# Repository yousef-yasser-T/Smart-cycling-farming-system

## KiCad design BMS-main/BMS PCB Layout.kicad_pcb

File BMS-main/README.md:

# BMS
# EV Battery Management System

Hardware design of a Battery Management System for Electric Vehicle applications.

## Overview

Designed the BMS schematic and PCB using KiCad, with manufacturing-ready Gerber files.

## Key Features

- Cell voltage monitoring
- Battery protection
- Temperature monitoring
- Current monitoring
- Cell balancing
- BMS control and monitoring

## Design

- Schematic: KiCad
- PCB Layout: KiCad
- Manufacturing: Gerber files
- BMS IC: TI BQ76920

## Files

| File | Description |
|---|---|
| `.kicad_sch` | BMS schematic |
| `.kicad_pcb` | PCB layout |
| `.zip` | Gerber manufacturing files |
| `.pdf` | BQ76920 datasheet |

## Focus Areas

**EV Systems | BMS | PCB Design | Battery Electronics | Embedded Systems**

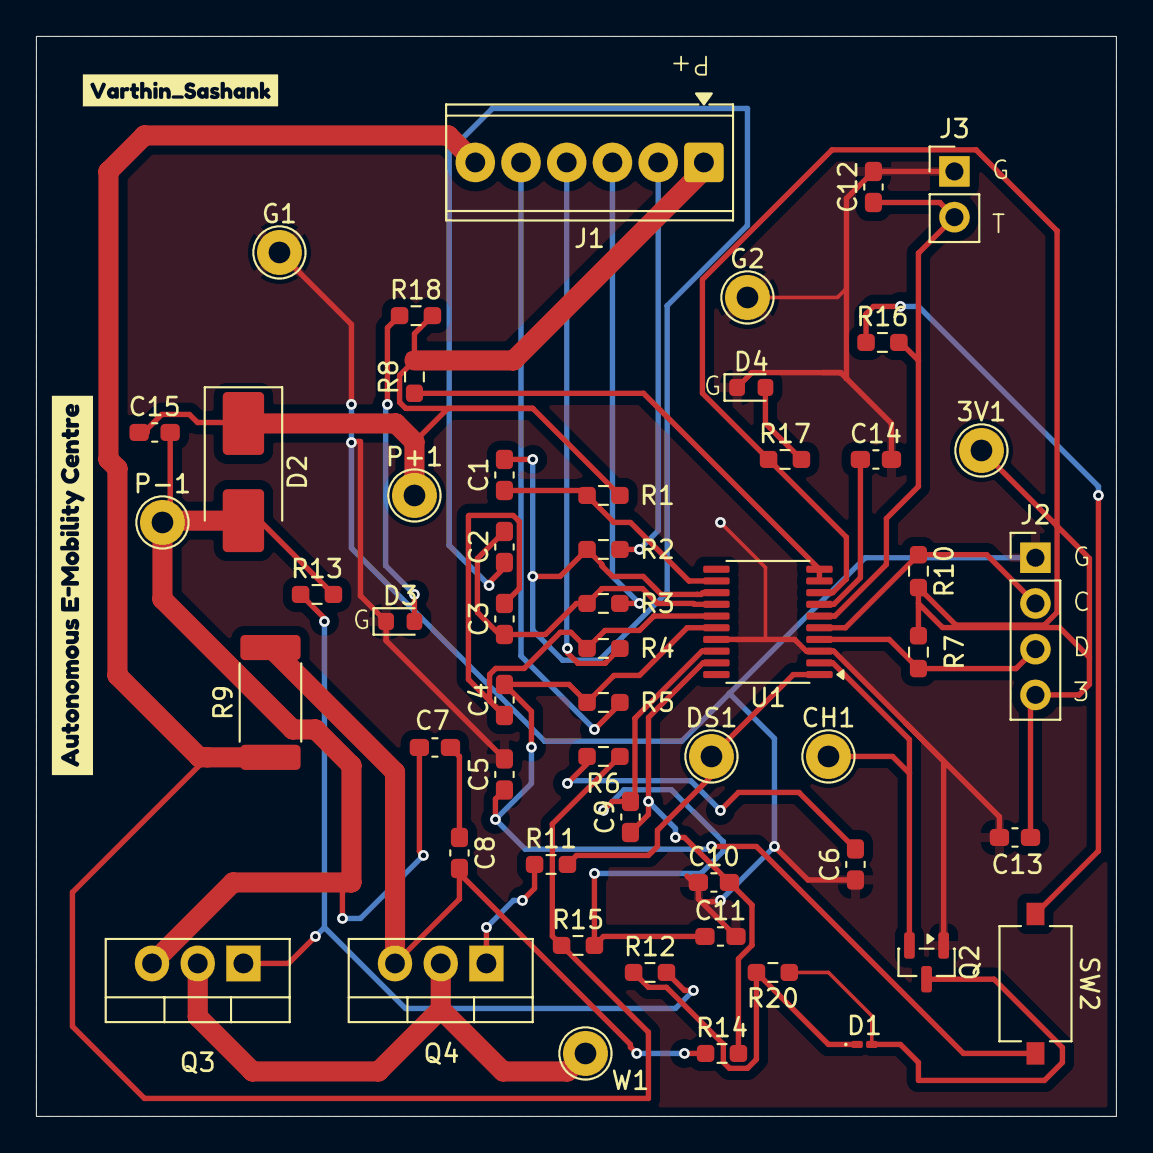
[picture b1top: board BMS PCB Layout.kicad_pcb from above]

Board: 2 copper layers, 60.0 x 60.0 mm, 56 parts (0 on the bottom side), 34 nets.

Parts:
3V1: TestPoint; TestPoint_THTPad_D2.5mm_Drill1.2mm
C1, C2, C3, C4, C5, C6, C9, C10, C11, C12, C14: 1uf; C_0603_1608Metric_Pad1.08x0.95mm_HandSolder
C7, C8: 0.1uf; C_0603_1608Metric_Pad1.08x0.95mm_HandSolder
C13: 4.7k; C_0603_1608Metric_Pad1.08x0.95mm_HandSolder
C15: 2.2uf; C_0603_1608Metric_Pad1.08x0.95mm_HandSolder
CH1: TestPoint; TestPoint_THTPad_D2.5mm_Drill1.2mm
D1: D; D_0201_0603Metric_Pad0.64x0.40mm_HandSolder
D2: 30V; D_SMB_Handsoldering
D3: ICE BLUE; LED_0603_1608Metric
D4: GREEN; LED_0603_1608Metric
DS1: TestPoint; TestPoint_THTPad_D2.5mm_Drill1.2mm
G1, G2: TestPoint; TestPoint_THTPad_D2.5mm_Drill1.2mm
J1: Screw_Terminal_01x06; TerminalBlock_Phoenix_MPT-0,5-6-2.54_1x06_P2.54mm_Horizontal
J2: Conn_01x04_Pin; PinHeader_1x04_P2.54mm_Vertical
J3: Conn_01x02_Pin; PinHeader_1x02_P2.54mm_Vertical
P+1: TestPoint; TestPoint_THTPad_D2.5mm_Drill1.2mm
P-1: TestPoint; TestPoint_THTPad_D2.5mm_Drill1.2mm
Q2: Si2371EDS; SOT-23
Q3, Q4: IRLZ44N; TO-220-3_Vertical
R1, R2, R3, R4, R5, R6, R8, R11, R12, R14, R15, R20: 100; R_0603_1608Metric_Pad0.98x0.95mm_HandSolder
R7, R10: 4.7K; R_0603_1608Metric_Pad0.98x0.95mm_HandSolder
R9: 0.005; R_2512_6332Metric_Pad1.40x3.35mm_HandSolder
R13: 1000; R_0603_1608Metric_Pad0.98x0.95mm_HandSolder
R16: 3.1k; R_0603_1608Metric_Pad0.98x0.95mm_HandSolder
R17: 470; R_0603_1608Metric_Pad0.98x0.95mm_HandSolder
R18: 4.7k; R_0603_1608Metric_Pad0.98x0.95mm_HandSolder
SW2: SW_Push; SW_Tactile_SPST_NO_Straight_CK_PTS636Sx25SMTRLFS
U1: BQ76920PW; TSSOP-20_4.4x6.5mm_P0.65mm
W1: TestPoint; TestPoint_THTPad_D2.5mm_Drill1.2mm
kibuzzard-69E92F47: G***; kibuzzard-69E92F47
kibuzzard-69E93592: G***; kibuzzard-69E93592

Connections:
+3.3V: 3V1.1, C13.1, J2.4, R7.2, R10.2, R17.1, U1.8 (REGOUT)
BATT-: J1.6, R6.2, R9.1, R15.1
CHG: CH1.1, Q2.2 (S), U1.2 (CHG)
DSG: DS1.1, R11.2, U1.1 (DSG)
GND: C5.2, C6.1, C10.1, C11.2, C12.2, C13.2, C14.2, D3.1 (K), D4.1 (K), G1.1, G2.1, J2.1, J3.1, Q2.1 (G), U1.3 (VSS), U1.17 (VC0)
unnamed: C6.2, R6.1
unnamed: C7.2, C8.1
unnamed: D1.2 (A), Q2.3 (D), R20.1
unnamed: D1.1 (K), R12.1, R20.2
unnamed: D3.2 (A), R18.1
unnamed: D4.2 (A), R17.2
unnamed: J1.2, R2.2
unnamed: J1.3, R3.2
unnamed: J1.4, R4.2
unnamed: J1.5, R5.2
unnamed: Q3.2 (D), Q4.2 (D), W1.1
unnamed: Q3.1 (G), R12.2, R13.1
unnamed: Q4.1 (G), R11.1
unnamed: R16.1, SW2.1
unnamed: R8.1, U1.9 (REGSRC), U1.10 (BAT)
unnamed: C4.2, C5.1, R5.1, SW2.2, U1.16 (VC1)
unnamed: C3.2, C4.1, R4.1, U1.15 (VC2)
unnamed: C2.2, C3.1, R3.1, U1.14 (VC3)
unnamed: C1.2, C2.1, R2.1, U1.13 (VC4)
unnamed: C1.1, R1.1, U1.12 (VC5)
PACK: C8.2, Q4.3 (S), R9.2, R14.1
Pack +: C15.1, D2.1 (K), J1.1, P+1.1, R1.2, R8.2, R18.2
Pack -: C7.1, C15.2, D2.2 (A), P-1.1, Q3.3 (S), R13.2
SCL: J2.2, R10.1, U1.5 (SCL)
SDA: J2.3, R7.1, U1.4 (SDA)
SRN: C9.1, C10.2, R14.2, U1.19 (SRN)
SRP: C9.2, C11.1, R15.2, U1.18 (SRP)
TS: C12.1, J3.2, R16.2, U1.6 (TS1)
cap: C14.1, U1.7 (CAP1)
